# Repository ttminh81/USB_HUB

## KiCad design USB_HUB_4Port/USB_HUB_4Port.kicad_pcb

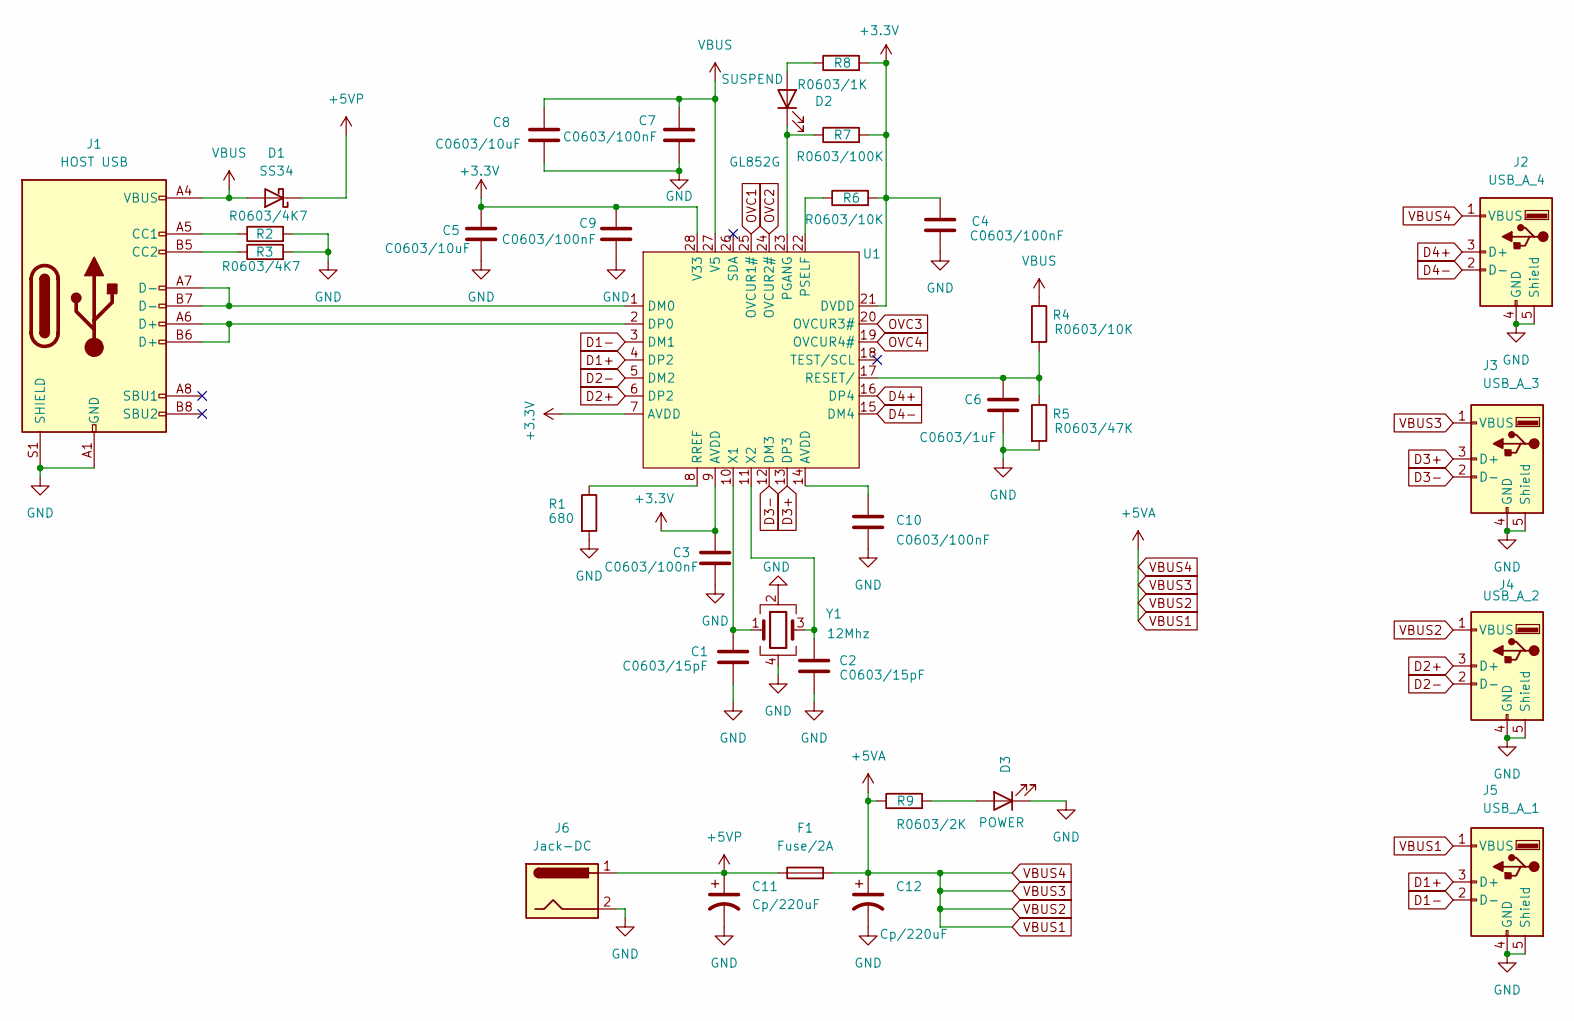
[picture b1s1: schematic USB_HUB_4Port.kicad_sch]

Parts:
C1, C2: C0603/15pF; C_0603_1608Metric
C3, C4, C7, C9, C10: C0603/100nF; C_0603_1608Metric
C5, C8: C0603/10uF; C_0603_1608Metric
C6: C0603/1uF; C_0603_1608Metric
C11, C12: Cp/220uF; CP_Elec_6.3x5.4
D1: SS34; D_SMA
D2: SUSPEND; LED_0603_1608Metric
D3: POWER; LED_D3.0mm
F1: Fuse/2A; Fuse_0805_2012Metric
J1: HOST USB; USB_C_Receptacle_G-Switch_GT-USB-7010ASV
J2: USB_A_4; USB_A_Molex_67643_Horizontal
J3: USB_A_3; USB_A_Molex_67643_Horizontal
J4: USB_A_2; USB_A_Molex_67643_Horizontal
J5: USB_A_1; USB_A_Molex_67643_Horizontal
J6: Jack-DC; BarrelJack_Horizontal
R1: 680; R_0603_1608Metric
R2, R3: R0603/4K7; R_0603_1608Metric
R4, R6: R0603/10K; R_0603_1608Metric
R5: R0603/47K; R_0603_1608Metric
R7: R0603/100K; R_0603_1608Metric
R8: R0603/1K; R_0603_1608Metric
R9: R0603/2K; R_0603_1608Metric
U1: GL852G; QFN-28-1EP_5x5mm_P0.5mm_EP3.1x3.1mm
Y1: 12Mhz; Oscillator_SMD_Abracon_ASE-4Pin_3.2x2.5mm

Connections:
+3.3V: C3.1, C4.1, C5.1, C9.1, R6.2, R7.2, R8.2, U1.7 (AVDD), U1.9 (AVDD), U1.21 (DVDD), U1.28 (V33)
+5VP: C11.1, D1.1 (K), F1.1, J6.1
D1+: J5.3 (D+), U1.4 (DP2)
D1-: J5.2 (D-), U1.3 (DM1)
D2+: J4.3 (D+), U1.6 (DP2)
D2-: J4.2 (D-), U1.5 (DM2)
D3+: J3.3 (D+), U1.13 (DP3)
D3-: J3.2 (D-), U1.12 (DM3)
D4+: J2.3 (D+), U1.16 (DP4)
D4-: J2.2 (D-), U1.15 (DM4)
GND: C1.2, C2.2, C3.2, C4.2, C5.2, C6.2, C7.2, C8.2, C9.2, C10.2, C11.2, C12.2, D3.1 (K), J1.A1 (GND), J1.A12 (GND), J1.B1 (GND), J1.B12 (GND), J1.S1 (SHIELD), J2.4 (GND), J2.5 (Shield), J3.4 (GND), J3.5 (Shield), J4.4 (GND), J4.5 (Shield), J5.4 (GND), J5.5 (Shield), J6.2, R1.2, R2.2, R3.2, R5.2, Y1.2, Y1.4
unnamed: C10.1, U1.14 (AVDD)
unnamed: D2.2 (A), R8.1
unnamed: D2.1 (K), R7.1, U1.23 (PGANG)
unnamed: D3.2 (A), R9.2
unnamed: J1.A5 (CC1), R2.1
unnamed: J1.B5 (CC2), R3.1
unnamed: J1.A7 (D-), J1.B7 (D-), U1.1 (DM0)
unnamed: J1.A6 (D+), J1.B6 (D+), U1.2 (DP0)
unnamed: R6.1, U1.22 (PSELF)
unnamed: C6.1, R4.2, R5.1, U1.17 (RESET/)
unnamed: R1.1, U1.8 (RREF)
unnamed: C1.1, U1.10 (X1), Y1.1
unnamed: C2.1, U1.11 (X2), Y1.3
OVC1: U1.25 (OVCUR1#)
OVC2: U1.24 (OVCUR2#)
OVC3: U1.20 (OVCUR3#)
OVC4: U1.19 (OVCUR4#)
VBUS: C7.1, C8.1, D1.2 (A), J1.A4 (VBUS), J1.A9 (VBUS), J1.B4 (VBUS), J1.B9 (VBUS), R4.1, U1.27 (V5)
VBUS1: C12.1, F1.2, J2.1 (VBUS), J3.1 (VBUS), J4.1 (VBUS), J5.1 (VBUS), R9.1

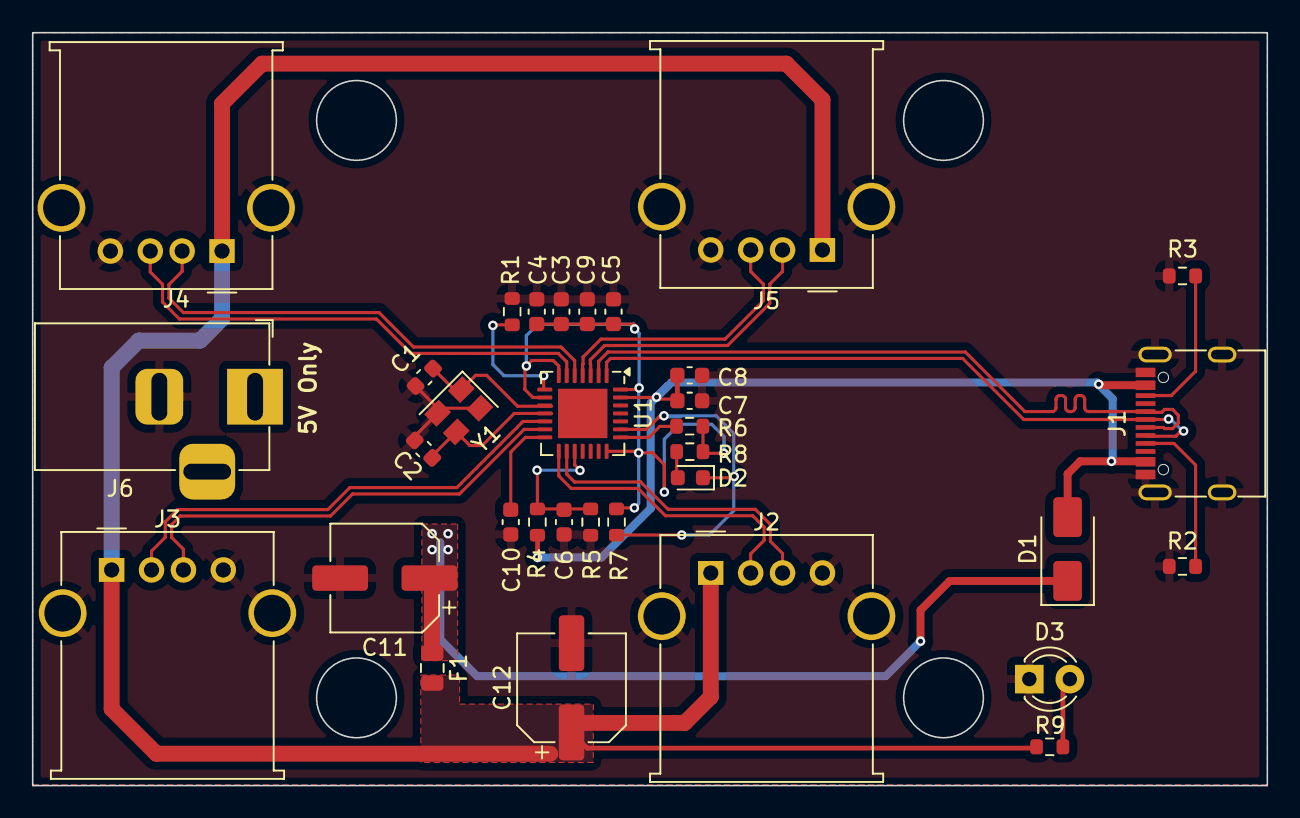
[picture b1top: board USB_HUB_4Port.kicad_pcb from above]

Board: 2 copper layers, 77.4 x 47.2 mm, 33 parts (0 on the bottom side), 26 nets.

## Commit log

2025-04-24 USB hub Added
2025-08-13 Add project 4 hub usb
